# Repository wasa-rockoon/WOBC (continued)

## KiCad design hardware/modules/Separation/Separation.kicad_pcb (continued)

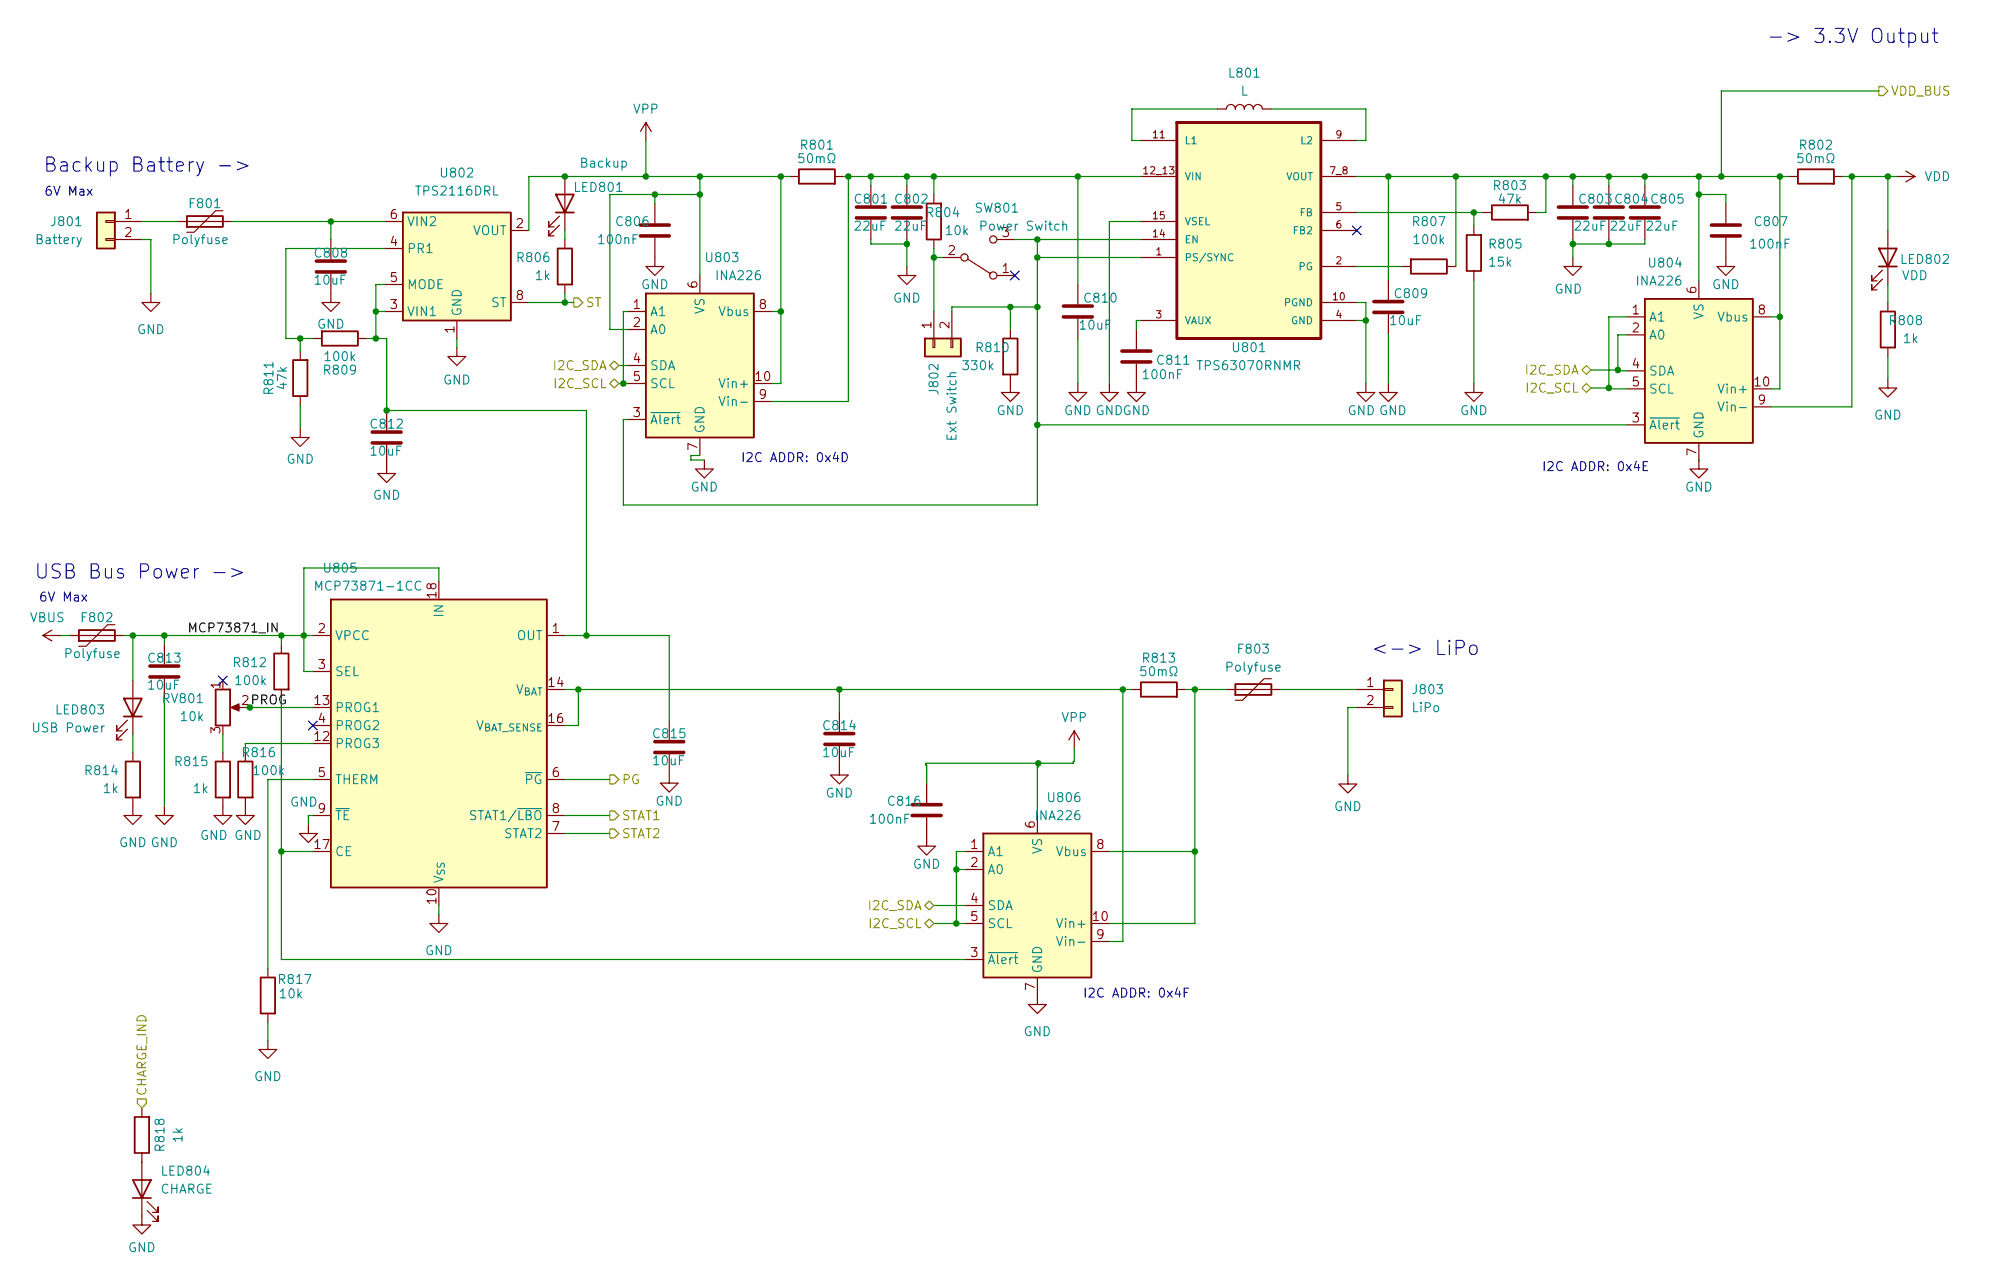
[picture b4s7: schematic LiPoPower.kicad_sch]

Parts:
C801, C802, C803, C804, C805: 22uF; C_0805_2012Metric; LCSC C45783
C806, C807, C811, C816: 100nF; C_0402_1005Metric; LCSC C1525
C808, C809, C810, C812, C813, C814, C815: 10uF; C_0603_1608Metric; LCSC C96446
F801, F802, F803: Polyfuse; Fuse_1206_3216Metric; LCSC C883133
J801: Battery; JST_XH_S2B-XH-A_1x02_P2.50mm_Horizontal
J802: Ext Switch; JST_PH_S2B-PH-K_1x02_P2.00mm_Horizontal
J803: LiPo; JST_PH_S2B-PH-K_1x02_P2.00mm_Horizontal
L801: L; L_Wuerth_WE-TPC-3816; LCSC C3033018
LED801: Backup; LED_0805_2012Metric; LCSC C2296
LED802: VDD; LED_0805_2012Metric; LCSC C2297
LED803: USB Power; LED_0805_2012Metric; LCSC C2297
LED804: CHARGE; LED_0805_2012Metric; LCSC C2296
R801, R802, R813: 50mΩ; R_0805_2012Metric; LCSC C247602
R803, R811: 47k; R_0402_1005Metric; LCSC C25792
R804, R817: 10k; R_0402_1005Metric; LCSC C25744
R805: 15k; R_0402_1005Metric; LCSC C25756
R806, R808, R814, R815, R818: 1k; R_0402_1005Metric; LCSC C11702
R807, R809, R812, R816: 100k; R_0402_1005Metric; LCSC C25741
R810: 330k; R_0402_1005Metric; LCSC C23137
RV801: 10k; Potentiometer_Bourns_TC33X_Vertical; LCSC C719176
SW801: Power Switch; SW_Slide_SPDT_Angled_CK_OS102011MA1Q
U801: TPS63070RNMR; VREG_TPS63070RNMR; LCSC C109322
U802: TPS2116DRL; SOT-583-8
U803, U804, U806: INA226; VSSOP-10_3x3mm_P0.5mm; LCSC C49851
U805: MCP73871-1CC; QFN-20-1EP_4x4mm_P0.5mm_EP2.5x2.5mm; LCSC C511310

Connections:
/ESP32core/GPIO4/ADC1_CH3: U805.6 (~PG); also elsewhere on the board
/ESP32core/GPIO5/ADC1_CH4: R806.2, U802.8 (ST); also elsewhere on the board
/ESP32core/GPIO6/ADC1_CH5: U805.8 (STAT1/~LBO); also elsewhere on the board
/LiPoPower/MCP73871_IN: C813.1, F802.2, LED803.2 (A), R812.1, U805.2 (VPCC), U805.3 (SEL), U805.18 (IN), U805.19 (IN)
/LiPoPower/PROG: RV801.2, U805.13 (PROG1)
/LiPoPower/STAT2: U805.7 (STAT2)
/LiPoPower/VDD_BUS: C803.1, C804.1, C805.1, C807.1, C809.1, R802.1, R803.2, R807.1, U801.7_8 (VOUT), U804.6 (VS), U804.8 (Vbus), U804.10 (Vin+)
/SCL: U803.1 (A1), U803.5 (SCL), U804.1 (A1), U804.5 (SCL), U806.1 (A1), U806.2 (A0), U806.5 (SCL); also elsewhere on the board
/SDA: U803.4 (SDA), U804.2 (A0), U804.4 (SDA), U806.4 (SDA); also elsewhere on the board
GND: C801.2, C802.2, C803.2, C804.2, C805.2, C806.2, C807.2, C808.2, C809.2, C810.2, C811.2, C812.2, C813.2, C814.2, C815.2, C816.2, J801.2, J803.2, LED804.1 (K), R805.1, R808.2, R810.2, R811.1, R814.2, R815.2, R816.2, R817.2, U801.4 (GND), U801.10 (PGND), U801.15 (VSEL), U802.1 (GND), U803.7 (GND), U804.7 (GND), U805.9 (~TE), U805.10 (V_{SS}), U805.11 (V_{SS}), U805.21 (V_{SS}), U806.7 (GND); also elsewhere on the board
unnamed: F801.1, J801.1
unnamed: J802.1, R804.1, SW801.2 (B)
unnamed: J802.2, R810.1, SW801.3 (C), U801.1 (PS/SYNC), U801.14 (EN), U803.3 (~Alert), U804.3 (~Alert)
unnamed: F803.2, J803.1
unnamed: LED801.1 (K), R806.1
unnamed: LED802.1 (K), R808.1
unnamed: LED803.1 (K), R814.1
unnamed: LED804.2 (A), R818.1
unnamed: R815.1, RV801.3
unnamed: R803.1, R805.2, U801.5 (FB)
unnamed: L801.1, U801.11 (L1)
unnamed: L801.2, U801.9 (L2)
unnamed: R807.2, U801.2 (PG)
unnamed: C811.1, U801.3 (VAUX)
unnamed: C801.1, C802.1, C810.1, R801.2, R804.2, U801.12_13 (VIN), U803.9 (Vin-)
unnamed: C812.1, C815.1, R809.1, U802.3 (VIN1), U802.5 (MODE), U805.1 (OUT), U805.20 (OUT)
unnamed: R809.2, R811.2, U802.4 (PR1)
unnamed: C808.1, F801.2, U802.6 (VIN2)
unnamed: R812.2, U805.17 (CE), U806.3 (~Alert)
unnamed: R816.1, U805.12 (PROG3)
unnamed: R817.1, U805.5 (THERM)
unnamed: C814.1, R813.1, U805.14 (V_{BAT}), U805.15 (V_{BAT}), U805.16 (V_{BAT_SENSE}), U806.9 (Vin-)
unnamed: F803.1, R813.2, U806.8 (Vbus), U806.10 (Vin+)
VBUS: F802.1; also elsewhere on the board
VDD: LED802.2 (A), R802.2, R818.2, U804.9 (Vin-); also elsewhere on the board
VPP: C806.1, C816.1, LED801.2 (A), R801.1, U802.2 (VOUT), U802.7 (VOUT), U803.2 (A0), U803.6 (VS), U803.8 (Vbus), U803.10 (Vin+), U806.6 (VS)

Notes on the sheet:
6V Max
USB Bus Power ->
<-> LiPo
I2C ADDR: 0x4D
I2C ADDR: 0x4F
-> 3.3V Output
I2C ADDR: 0x4E
Backup Battery ->

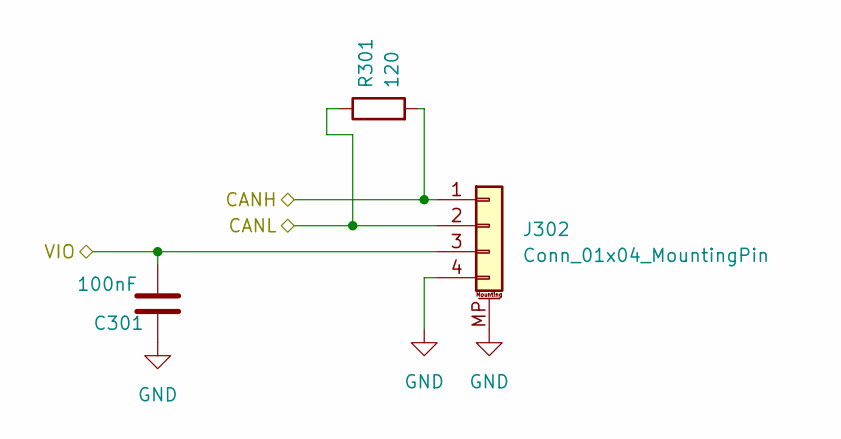
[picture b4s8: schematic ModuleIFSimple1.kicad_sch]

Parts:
C301: 100nF; C_0402_1005Metric; LCSC C1525
J302: Conn_01x04_MountingPin; Grove_4P_L_SMD
R301: 120; R_0402_1005Metric; LCSC C25079

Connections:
/CANH: J302.1, R301.2; also elsewhere on the board
/CANL: J302.2, R301.1; also elsewhere on the board
GND: C301.1, J302.4, J302.MP (MountPin); also elsewhere on the board
VDD: C301.2, J302.3; also elsewhere on the board

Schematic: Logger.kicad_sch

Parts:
C601: 100nF; C_0402_1005Metric; LCSC C1525
C602: 10uF; C_0603_1608Metric; LCSC C96446
MICRO_SD601: TF-01A; LCSC C5155563
U601: PCF8563T; SOIC-8_3.9x4.9mm_P1.27mm; LCSC C7440
Y601: Crystal; Crystal_SMD_3215-2Pin_3.2x1.5mm; LCSC C32346

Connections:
/CS: MICRO_SD601.2 (CD/DAT3); also elsewhere on the board
/DET: MICRO_SD601.CD1 (CD); also elsewhere on the board
/MISO: MICRO_SD601.7 (DAT0); also elsewhere on the board
/MOSI: MICRO_SD601.3 (CMD); also elsewhere on the board
/SCK: MICRO_SD601.5 (CLK); also elsewhere on the board
/SCL: U601.6 (SCL); also elsewhere on the board
/SDA: U601.5 (SDA); also elsewhere on the board
GND: C601.1, C602.2, MICRO_SD601.6 (VSS), MICRO_SD601.MP1 (SHIELD), MICRO_SD601.MP2 (SHIELD), MICRO_SD601.MP3 (SHIELD), MICRO_SD601.MP4 (SHIELD), U601.4 (VSS); also elsewhere on the board
unnamed: U601.1 (OSCI), Y601.1
unnamed: U601.2 (OSCO), Y601.2
VDD: C601.2, C602.1, MICRO_SD601.4 (VDD), U601.8 (VDD); also elsewhere on the board

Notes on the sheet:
Micro SD Card Slot
RTC
I2C ADDR: 0x51

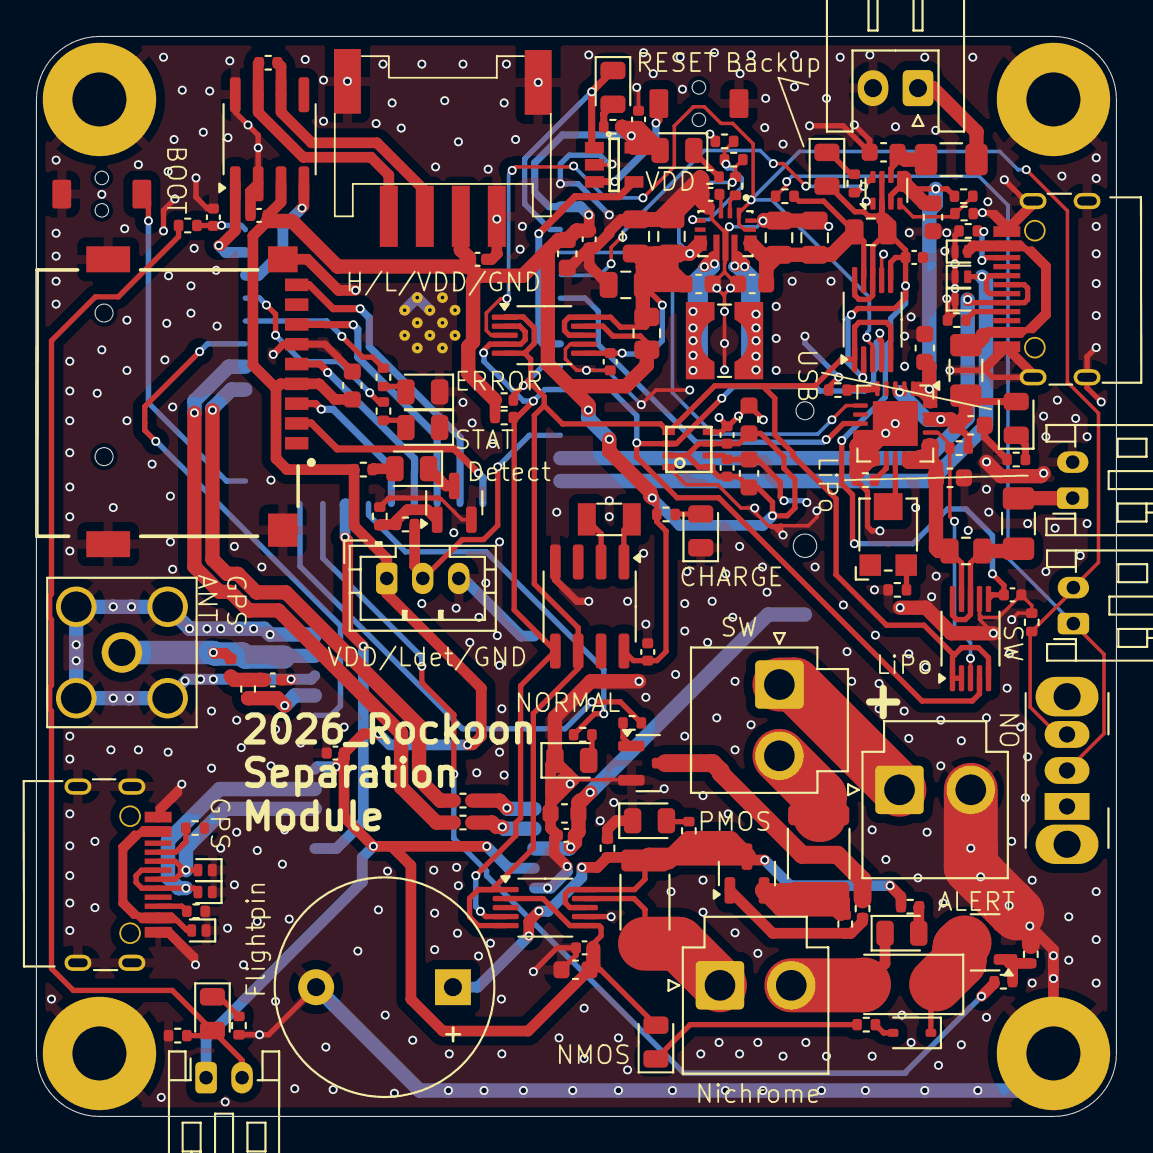
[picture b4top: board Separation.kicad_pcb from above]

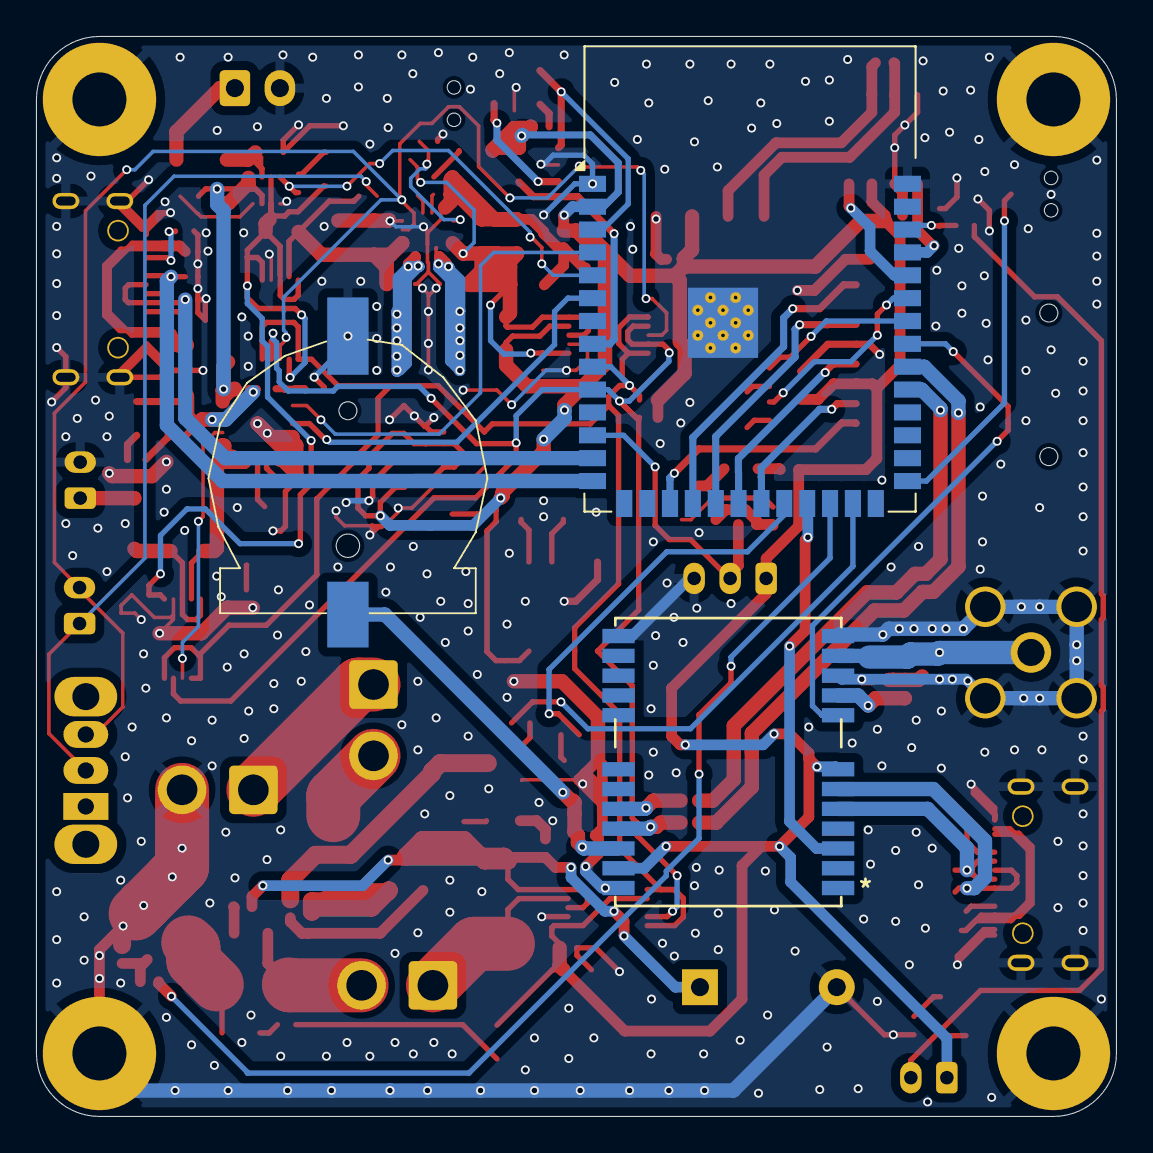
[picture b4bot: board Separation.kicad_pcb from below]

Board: 2 copper layers, 60.0 x 60.0 mm, 147 parts (3 on the bottom side), 100 nets.

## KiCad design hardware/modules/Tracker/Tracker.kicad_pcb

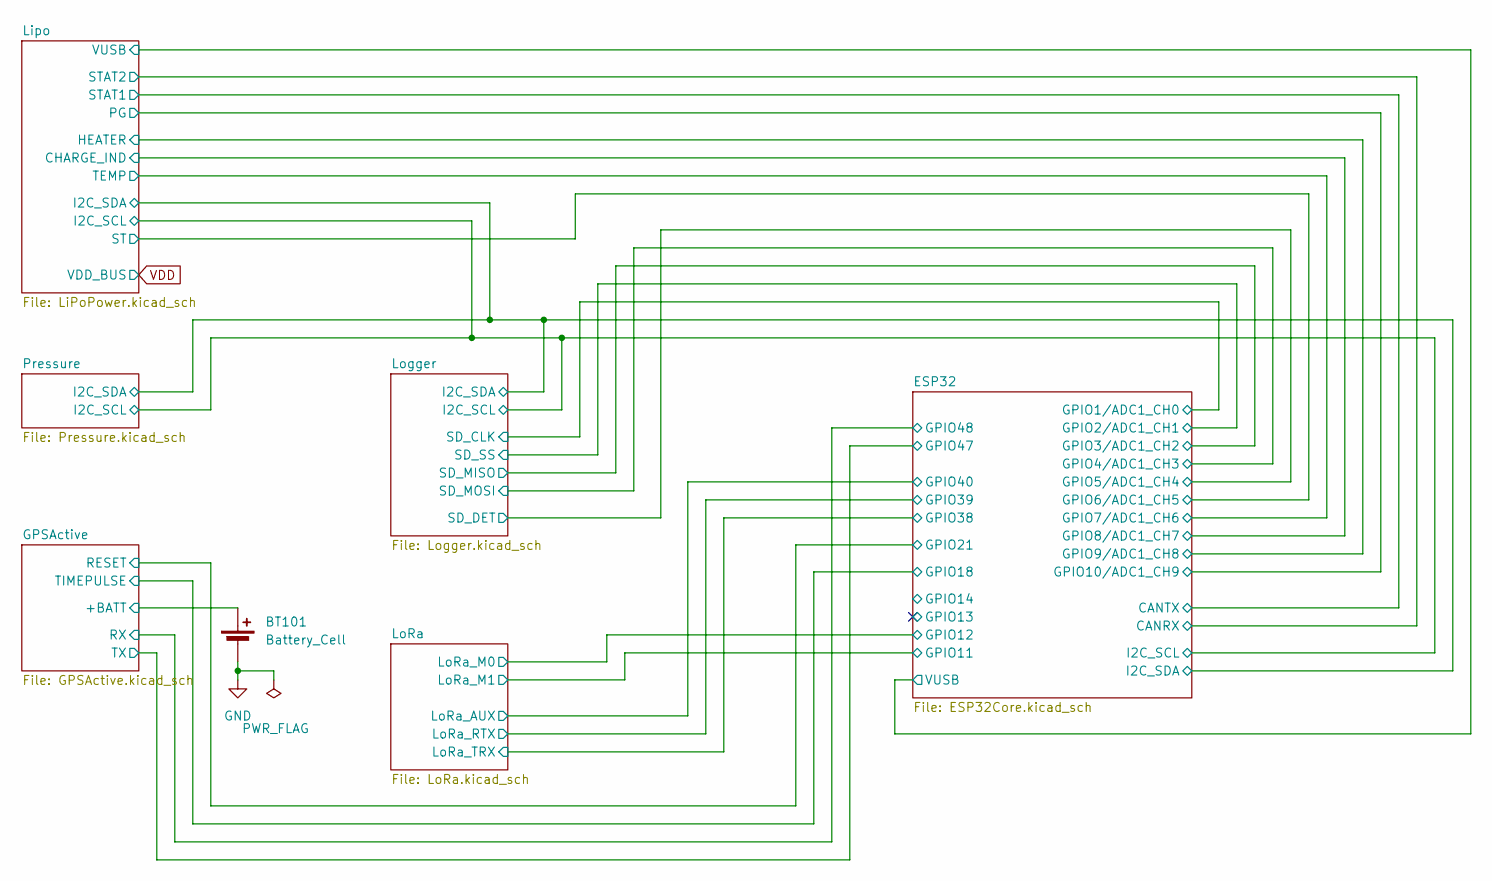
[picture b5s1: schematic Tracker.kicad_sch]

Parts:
BT101: Battery_Cell; cr1220

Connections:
/GPSActive/+BATT: BT101.1 (+); also elsewhere on the board
GND: BT101.2 (-); also elsewhere on the board

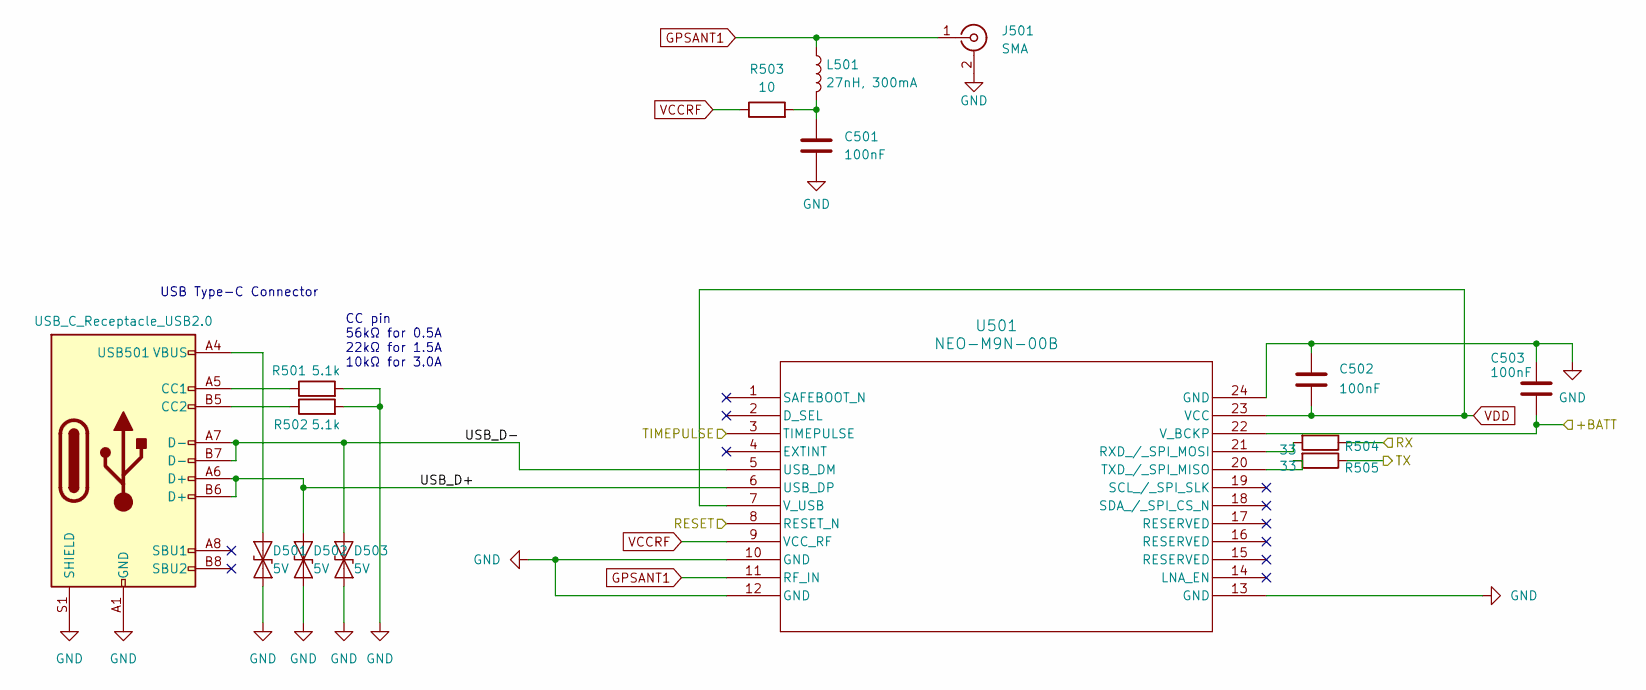
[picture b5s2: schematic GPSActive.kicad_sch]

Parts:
C501, C502: 100nF; C_0402_1005Metric; LCSC C1525
C503: 100nF; C_0402_1005Metric
D501, D502, D503: 5V; D_SOD-882D; LCSC C7420372
J501: SMA; SMA_Amphenol_132203-12_Horizontal; LCSC C2693813
L501: 27nH, 300mA; L_0402_1005Metric; LCSC C18830
R501, R502: 5.1k; R_0402_1005Metric; LCSC C25905
R503: 10; R_0402_1005Metric; LCSC C25077
R504, R505: 33; R_0402_1005Metric; LCSC C25105
U501: NEO-M9N-00B; ATGM332D-5N31
USB501: USB_C_Receptacle_USB2.0; USB_C_TYPEC-301S-ACP16X7; LCSC C2982481

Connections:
/ESP32/GPIO18: U501.3 (TIMEPULSE); also elsewhere on the board
/ESP32/GPIO21: U501.8 (RESET_N); also elsewhere on the board
/ESP32/GPIO47: R505.1; also elsewhere on the board
/ESP32/GPIO48: R504.1; also elsewhere on the board
/GPSActive/+BATT: C503.2, U501.22 (V_BCKP); also elsewhere on the board
/GPSActive/USB_D+: D502.2 (A2), U501.6 (USB_DP), USB501.A6 (D+), USB501.B6 (D+)
/GPSActive/USB_D-: D503.2 (A2), U501.5 (USB_DM), USB501.A7 (D-), USB501.B7 (D-)
GND: C501.2, C502.1, C503.1, D501.1 (A1), D502.1 (A1), D503.1 (A1), J501.2 (Ext), R501.2, R502.2, U501.10 (GND), U501.12 (GND), U501.13 (GND), U501.24 (GND), USB501.A1 (GND), USB501.A12 (GND), USB501.B1 (GND), USB501.B12 (GND), USB501.S1 (SHIELD); also elsewhere on the board
GPSANT1: J501.1 (In), L501.1, U501.11 (RF_IN)
unnamed: C501.1, L501.2, R503.2
unnamed: D501.2 (A2), USB501.A4 (VBUS), USB501.A9 (VBUS), USB501.B4 (VBUS), USB501.B9 (VBUS)
unnamed: R504.2, U501.21 (RXD_/_SPI_MOSI)
unnamed: R505.2, U501.20 (TXD_/_SPI_MISO)
unnamed: R501.1, USB501.A5 (CC1)
unnamed: R502.1, USB501.B5 (CC2)
VCCRF: R503.1, U501.9 (VCC_RF)
VDD: C502.2, U501.7 (V_USB), U501.23 (VCC); also elsewhere on the board

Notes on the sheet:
CC pin 56kΩ for 0.5A 22kΩ for 1.5A 10kΩ for 3.0A
USB Type-C Connector

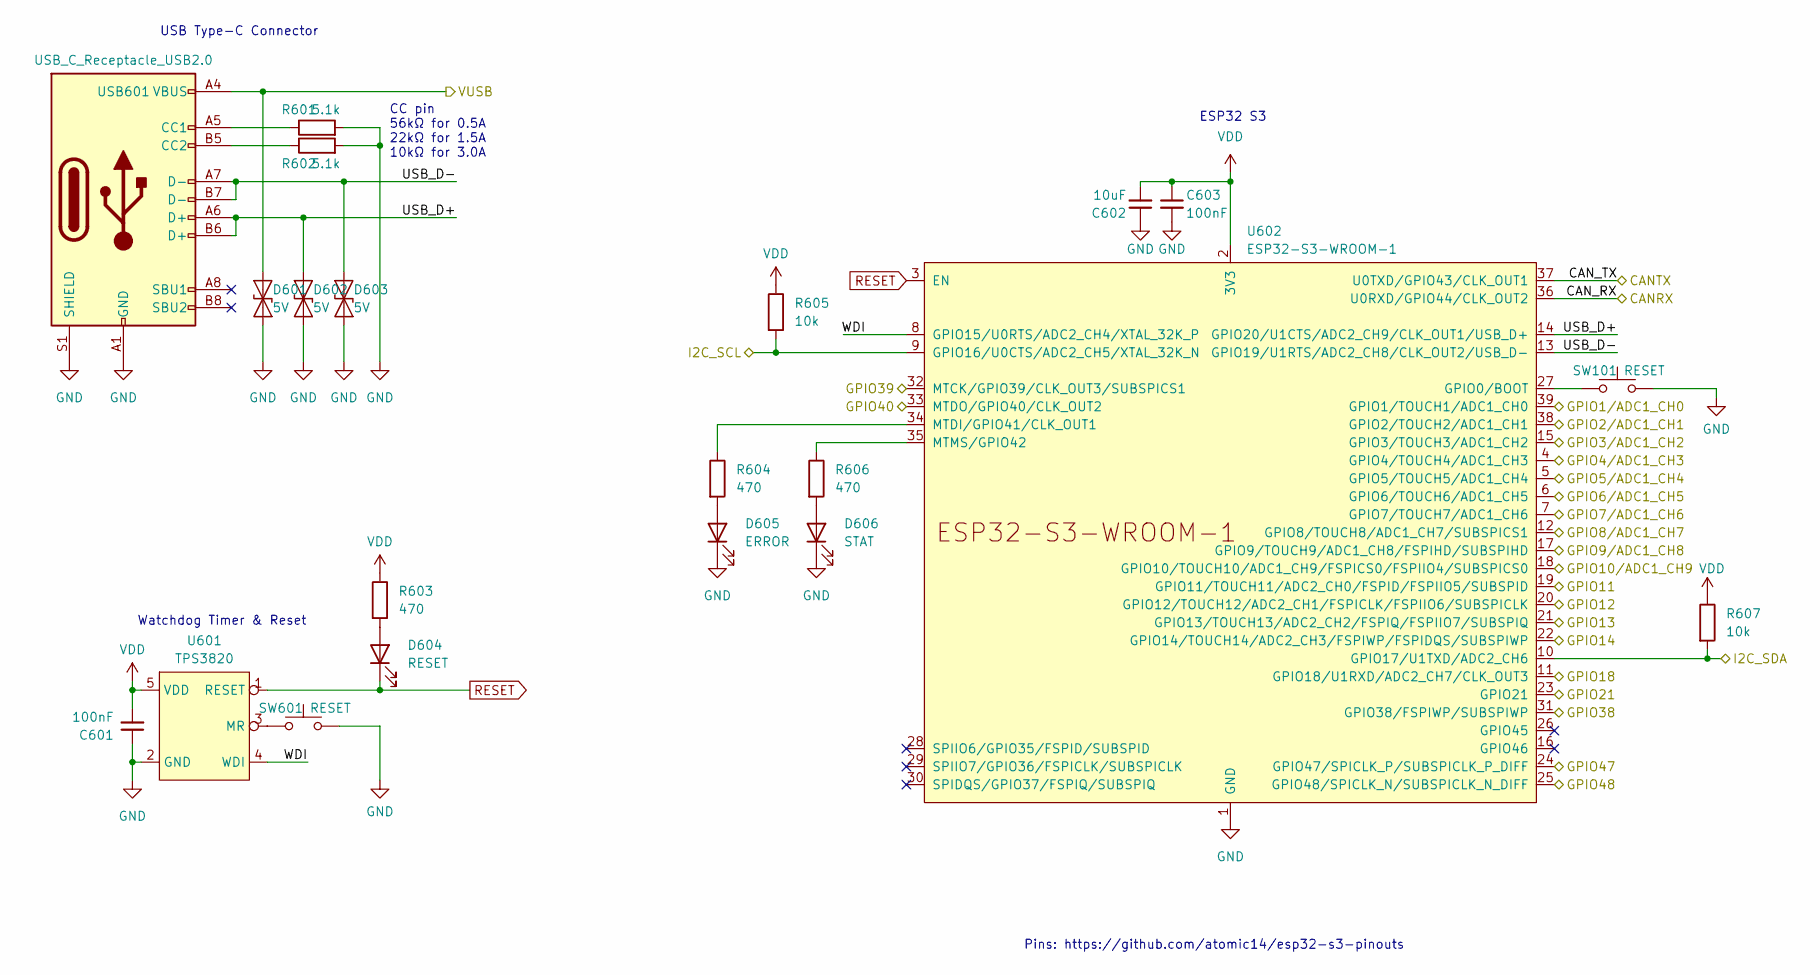
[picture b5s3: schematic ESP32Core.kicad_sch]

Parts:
C601, C603: 100nF; C_0402_1005Metric; LCSC C1525
C602: 10uF; C_0603_1608Metric; LCSC C96446
D601, D602, D603: 5V; D_SOD-882D; LCSC C7420372
D604: RESET; LED_0805_2012Metric; LCSC C2296
D605: ERROR; LED_0805_2012Metric; LCSC C84256
D606: STAT; LED_0805_2012Metric; LCSC C2297
R601, R602: 5.1k; R_0402_1005Metric; LCSC C25905
R603, R604, R606: 470; R_0402_1005Metric; LCSC C25117
R605, R607: 10k; R_0402_1005Metric; LCSC C25744
SW101, SW601: RESET; TVAF06-A020B-R
U601: TPS3820; SOT_23_5; LCSC C130064
U602: ESP32-S3-WROOM-1
USB601: USB_C_Receptacle_USB2.0; USB_C_TYPEC-301S-ACP16X7; LCSC C2982481

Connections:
/ESP32/CAN_RX: U602.36 (U0RXD/GPIO44/CLK_OUT2); also elsewhere on the board
/ESP32/CAN_TX: U602.37 (U0TXD/GPIO43/CLK_OUT1); also elsewhere on the board
/ESP32/GPIO1/ADC1_CH0: U602.39 (GPIO1/TOUCH1/ADC1_CH0); also elsewhere on the board
/ESP32/GPIO2/ADC1_CH1: U602.38 (GPIO2/TOUCH2/ADC1_CH1); also elsewhere on the board
/ESP32/GPIO3/ADC1_CH2: U602.15 (GPIO3/TOUCH3/ADC1_CH2); also elsewhere on the board
/ESP32/GPIO4/ADC1_CH3: U602.4 (GPIO4/TOUCH4/ADC1_CH3); also elsewhere on the board
/ESP32/GPIO5/ADC1_CH4: U602.5 (GPIO5/TOUCH5/ADC1_CH4); also elsewhere on the board
/ESP32/GPIO6/ADC1_CH5: U602.6 (GPIO6/TOUCH6/ADC1_CH5); also elsewhere on the board
/ESP32/GPIO7/ADC1_CH6: U602.7 (GPIO7/TOUCH7/ADC1_CH6); also elsewhere on the board
/ESP32/GPIO8/ADC1_CH7: U602.12 (GPIO8/TOUCH8/ADC1_CH7/SUBSPICS1); also elsewhere on the board
/ESP32/GPIO9/ADC1_CH8: U602.17 (GPIO9/TOUCH9/ADC1_CH8/FSPIHD/SUBSPIHD); also elsewhere on the board
/ESP32/GPIO10/ADC1_CH9: U602.18 (GPIO10/TOUCH10/ADC1_CH9/FSPICS0/FSPIIO4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); also elsewhere on the board
/ESP32/GPIO11: U602.19 (GPIO11/TOUCH11/ADC2_CH0/FSPID/FSPIIO5/S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); also elsewhere on the board
/ESP32/GPIO12: U602.20 (GPIO12/TOUCH12/ADC2_CH1/FSPICLK/FSPIIO6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); also elsewhere on the board
/ESP32/GPIO13: U602.21 (GPIO13/TOUCH13/ADC2_CH2/FSPIQ/FSPIIO7/S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)
/ESP32/GPIO14: U602.22 (GPIO14/TOUCH14/ADC2_CH3/FSPIWP/FSPIDQS/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)
/ESP32/GPIO18: U602.11 (GPIO18/U1RXD/ADC2_CH7/CLK_OUT3); also elsewhere on the board
/ESP32/GPIO21: U602.23 (GPIO21); also elsewhere on the board
/ESP32/GPIO38: U602.31 (GPIO38/FSPIWP/SUBSPIWP); also elsewhere on the board
/ESP32/GPIO39: U602.32 (MTCK/GPIO39/CLK_OUT3/SUBSPICS1); also elsewhere on the board
/ESP32/GPIO40: U602.33 (MTDO/GPIO40/CLK_OUT2); also elsewhere on the board
/ESP32/GPIO47: U602.24 (GPIO47/SPICLK_P/SUBSPICLK_P_DIFF); also elsewhere on the board
/ESP32/GPIO48: U602.25 (GPIO48/SPICLK_N/SUBSPICLK_N_DIFF); also elsewhere on the board
/ESP32/I2C_SCL: R605.2, U602.9 (GPIO16/U0CTS/ADC2_CH5/XTAL_32K_N); also elsewhere on the board
/ESP32/I2C_SDA: R607.2, U602.10 (GPIO17/U1TXD/ADC2_CH6); also elsewhere on the board
/ESP32/USB_D+: D602.2 (A2), U602.14 (GPIO20/U1CTS/ADC2_CH9/CLK_OUT1/USB_D+), USB601.A6 (D+), USB601.B6 (D+)
/ESP32/USB_D-: D603.2 (A2), U602.13 (GPIO19/U1RTS/ADC2_CH8/CLK_OUT2/USB_D-), USB601.A7 (D-), USB601.B7 (D-)
/ESP32/VUSB: D601.2 (A2), USB601.A4 (VBUS), USB601.A9 (VBUS), USB601.B4 (VBUS), USB601.B9 (VBUS); also elsewhere on the board
/ESP32/WDI: U601.4 (WDI), U602.8 (GPIO15/U0RTS/ADC2_CH4/XTAL_32K_P)
GND: C601.1, C602.1, C603.2, D601.1 (A1), D602.1 (A1), D603.1 (A1), D605.1 (K), D606.1 (K), R601.2, R602.2, SW101.2, SW601.2, U601.2 (GND), U602.1 (GND), U602.40 (GND), U602.41 (GND), USB601.A1 (GND), USB601.A12 (GND), USB601.B1 (GND), USB601.B12 (GND), USB601.S1 (SHIELD); also elsewhere on the board
unnamed: D604.2 (A), R603.2
unnamed: D605.2 (A), R604.2
unnamed: D606.2 (A), R606.2
unnamed: SW601.1, U601.3 (MR)
unnamed: SW101.1, U602.27 (GPIO0/BOOT)
unnamed: R604.1, U602.34 (MTDI/GPIO41/CLK_OUT1)
unnamed: R606.1, U602.35 (MTMS/GPIO42)
unnamed: R601.1, USB601.A5 (CC1)
unnamed: R602.1, USB601.B5 (CC2)
RESET: D604.1 (K), U601.1 (RESET), U602.3 (EN)
VDD: C601.2, C602.2, C603.1, R603.1, R605.1, R607.1, U601.5 (VDD), U602.2 (3V3); also elsewhere on the board

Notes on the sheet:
ESP32 S3
Watchdog Timer & Reset
Pins: https://github.com/atomic14/esp32-s3-pinouts
USB Type-C Connector
CC pin 56kΩ for 0.5A 22kΩ for 1.5A 10kΩ for 3.0A

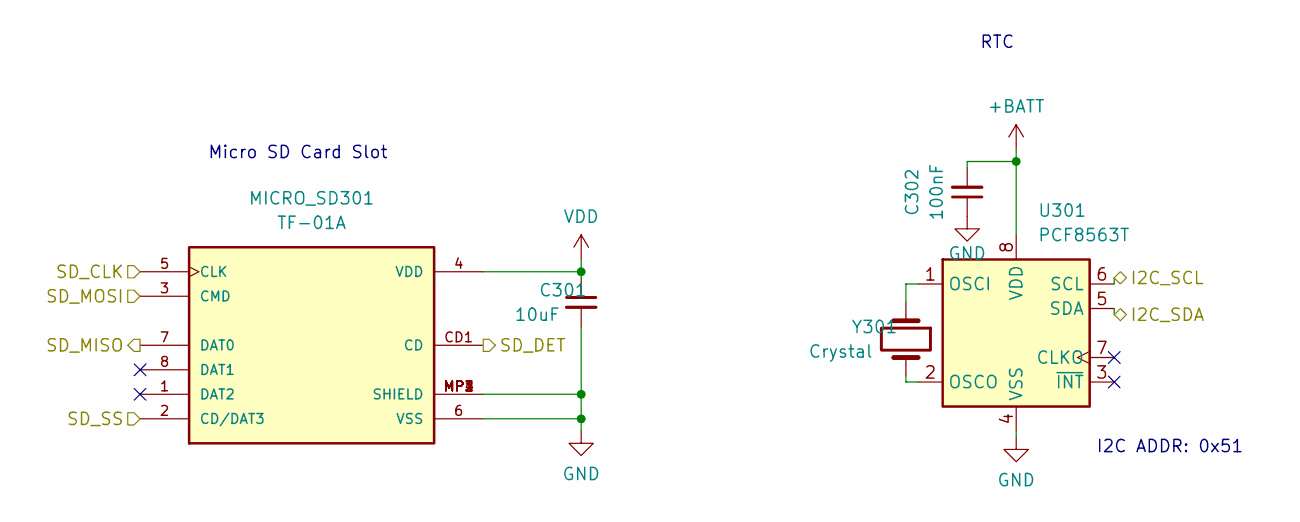
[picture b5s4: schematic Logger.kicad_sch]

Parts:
C301: 10uF; C_0603_1608Metric; LCSC C96446
C302: 100nF; C_0402_1005Metric; LCSC C1525
MICRO_SD301: TF-01A; LCSC C5155563
U301: PCF8563T; SOIC-8_3.9x4.9mm_P1.27mm; LCSC C5795601
Y301: Crystal; Crystal_SMD_3215-2Pin_3.2x1.5mm; LCSC C9002

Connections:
+BATT: C302.2, U301.8 (VDD)
/ESP32/GPIO1/ADC1_CH0: MICRO_SD301.5 (CLK); also elsewhere on the board
/ESP32/GPIO2/ADC1_CH1: MICRO_SD301.2 (CD/DAT3); also elsewhere on the board
/ESP32/GPIO3/ADC1_CH2: MICRO_SD301.7 (DAT0); also elsewhere on the board
/ESP32/GPIO4/ADC1_CH3: MICRO_SD301.3 (CMD); also elsewhere on the board
/ESP32/GPIO5/ADC1_CH4: MICRO_SD301.CD1 (CD); also elsewhere on the board
/ESP32/I2C_SCL: U301.6 (SCL); also elsewhere on the board
/ESP32/I2C_SDA: U301.5 (SDA); also elsewhere on the board
GND: C301.2, C302.1, MICRO_SD301.6 (VSS), MICRO_SD301.MP1 (SHIELD), MICRO_SD301.MP2 (SHIELD), MICRO_SD301.MP3 (SHIELD), MICRO_SD301.MP4 (SHIELD), U301.4 (VSS); also elsewhere on the board
unnamed: U301.1 (OSCI), Y301.1
unnamed: U301.2 (OSCO), Y301.2
VDD: C301.1, MICRO_SD301.4 (VDD); also elsewhere on the board

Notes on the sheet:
Micro SD Card Slot
RTC
I2C ADDR: 0x51
